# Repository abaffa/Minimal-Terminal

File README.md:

# Baffa Terminal (minimal-terminal clone) 

This is a Simple Terminal board based on "Minimal-Terminal" project by Carsten Herting (oct/2021 https://github.com/slu4coder/Minimal-Terminal).

Current version supports US-International keyboard mapping, four basic serial speeds (115200, 57600, 38400, 9600 BPS) and [supports some basic CSI/Ansi escapes](supported_escapes.md).
 
The prototype board has been tested with my CP/M machine (see http://baffa-2.baffasoft.com.br) but there is another board compatible with RC2014 pinout. 

### Video

## Baffa-2 Terminal Board:

[Order Baffa-2 Minimal Terminal PCB from PCBWay](https://www.pcbway.com/project/shareproject/Baffa_2_Minimal_Terminal_f85704c4.html)

## RC2014 Minimal-Terminal Module

[Order RC2014 Minimal Terminal PCB from PCBWay](https://www.pcbway.com/project/shareproject/RC2014_Minimal_Terminal_41593f8c.html)

## Bill of Materials

| Qty | Value | Parts | Description |
|:---:|:----------:|:-----|:-----|
| 1 |  PINHD-1X20 | JP4 |  PIN HEADER |
| 1 |  PINHD-1X40 | JP3 |  PIN HEADER |
| 6 |  100nf | C2, C6, C9, C10, C11, C12 | CAPACITOR |
| 2 |  10k | R10, R16 | RESISTOR |
| 1 | 150 | R13 | RESISTOR |
| 2 |  1k | R11, R12 | RESISTOR |
| 1 |  24Mhz XTAL |  XTAL |  XTAL SOCKET-14 |
| 1 |  330nf | C1 | CAPACITOR |
| 1 |  47uf | C7 | POLARIZED CAPACITOR |
| 1 |  74HC166N |  IC2 |  8-bit parallel load SHIFT REGISTER |
| 2 | 75 | R14, R15 | RESISTOR, American symbol |
| 1 |  7806T | IC1 |  Positive VOLTAGE REGULATOR |
| 2 |  ATMEGA328P-PU | UART_PS2, VGA |  PDIP-28 Atmel |
| 1 |  BUS UART | JP2 |  JUMPER |
| 1 |  MINI-DIN6PTH |  PS2_DIN |  mini DIN 6 Connector |
| 1 |  Power 9-12v | JP1 |  PIN HEADER |
| 1 |  RESET | S5 | MOM SWITCH |
| 1 |  SPEED | JP7 |  JUMPER |
| 1 | PINHD-1X6 | UART |  PIN HEADER |
| 1 | PINHD-1X6 |  VGA |  PIN HEADER |
| 1 | DSUB | VGA Output | SUB-D |
 
## License

Copyright (c) 2021 Augusto Baffa, Carsten Herting

Permission is hereby granted, free of charge, to any person obtaining a copy
of this software and associated documentation files (the "Software"), to deal
in the Software without restriction, including without limitation the rights
to use, copy, modify, merge, publish, distribute, sublicense, and/or sell
copies of the Software, and to permit persons to whom the Software is
furnished to do so, subject to the following conditions:

The above copyright notice and this permission notice shall be included in all
copies or substantial portions of the Software.

THE SOFTWARE IS PROVIDED "AS IS", WITHOUT WARRANTY OF ANY KIND, EXPRESS OR
IMPLIED, INCLUDING BUT NOT LIMITED TO THE WARRANTIES OF MERCHANTABILITY,
FITNESS FOR A PARTICULAR PURPOSE AND NONINFRINGEMENT. IN NO EVENT SHALL THE
AUTHORS OR COPYRIGHT HOLDERS BE LIABLE FOR ANY CLAIM, DAMAGES OR OTHER
LIABILITY, WHETHER IN AN ACTION OF CONTRACT, TORT OR OTHERWISE, ARISING FROM,
OUT OF OR IN CONNECTION WITH THE SOFTWARE OR THE USE OR OTHER DEALINGS IN THE
SOFTWARE.

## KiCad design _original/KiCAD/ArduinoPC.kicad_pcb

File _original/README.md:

## Original Minimal-Terminal Read.me

Minimal serial UART terminal with VGA and PS2 for up to 230400bps based upon ATmega328P.

This little gadget it ideally suited to be used together with the 'Minimal UART CPU System': https://github.com/slu4coder/Minimal-UART-CPU-System

See the manual section 'Native Tool Chain / Terminal' for more information:
https://docs.google.com/document/d/1c2ZHtLd1BBAwcBAjBZZJmCA3AXpbpv80dlAtsMYpuF4/edit?usp=sharing

---
MIT License

Copyright (c) 2021 Carsten Herting

Permission is hereby granted, free of charge, to any person obtaining a copy
of this software and associated documentation files (the "Software"), to deal
in the Software without restriction, including without limitation the rights
to use, copy, modify, merge, publish, distribute, sublicense, and/or sell
copies of the Software, and to permit persons to whom the Software is
furnished to do so, subject to the following conditions:

The above copyright notice and this permission notice shall be included in all
copies or substantial portions of the Software.

THE SOFTWARE IS PROVIDED "AS IS", WITHOUT WARRANTY OF ANY KIND, EXPRESS OR
IMPLIED, INCLUDING BUT NOT LIMITED TO THE WARRANTIES OF MERCHANTABILITY,
FITNESS FOR A PARTICULAR PURPOSE AND NONINFRINGEMENT. IN NO EVENT SHALL THE
AUTHORS OR COPYRIGHT HOLDERS BE LIABLE FOR ANY CLAIM, DAMAGES OR OTHER
LIABILITY, WHETHER IN AN ACTION OF CONTRACT, TORT OR OTHERWISE, ARISING FROM,
OUT OF OR IN CONNECTION WITH THE SOFTWARE OR THE USE OR OTHER DEALINGS IN THE
SOFTWARE.

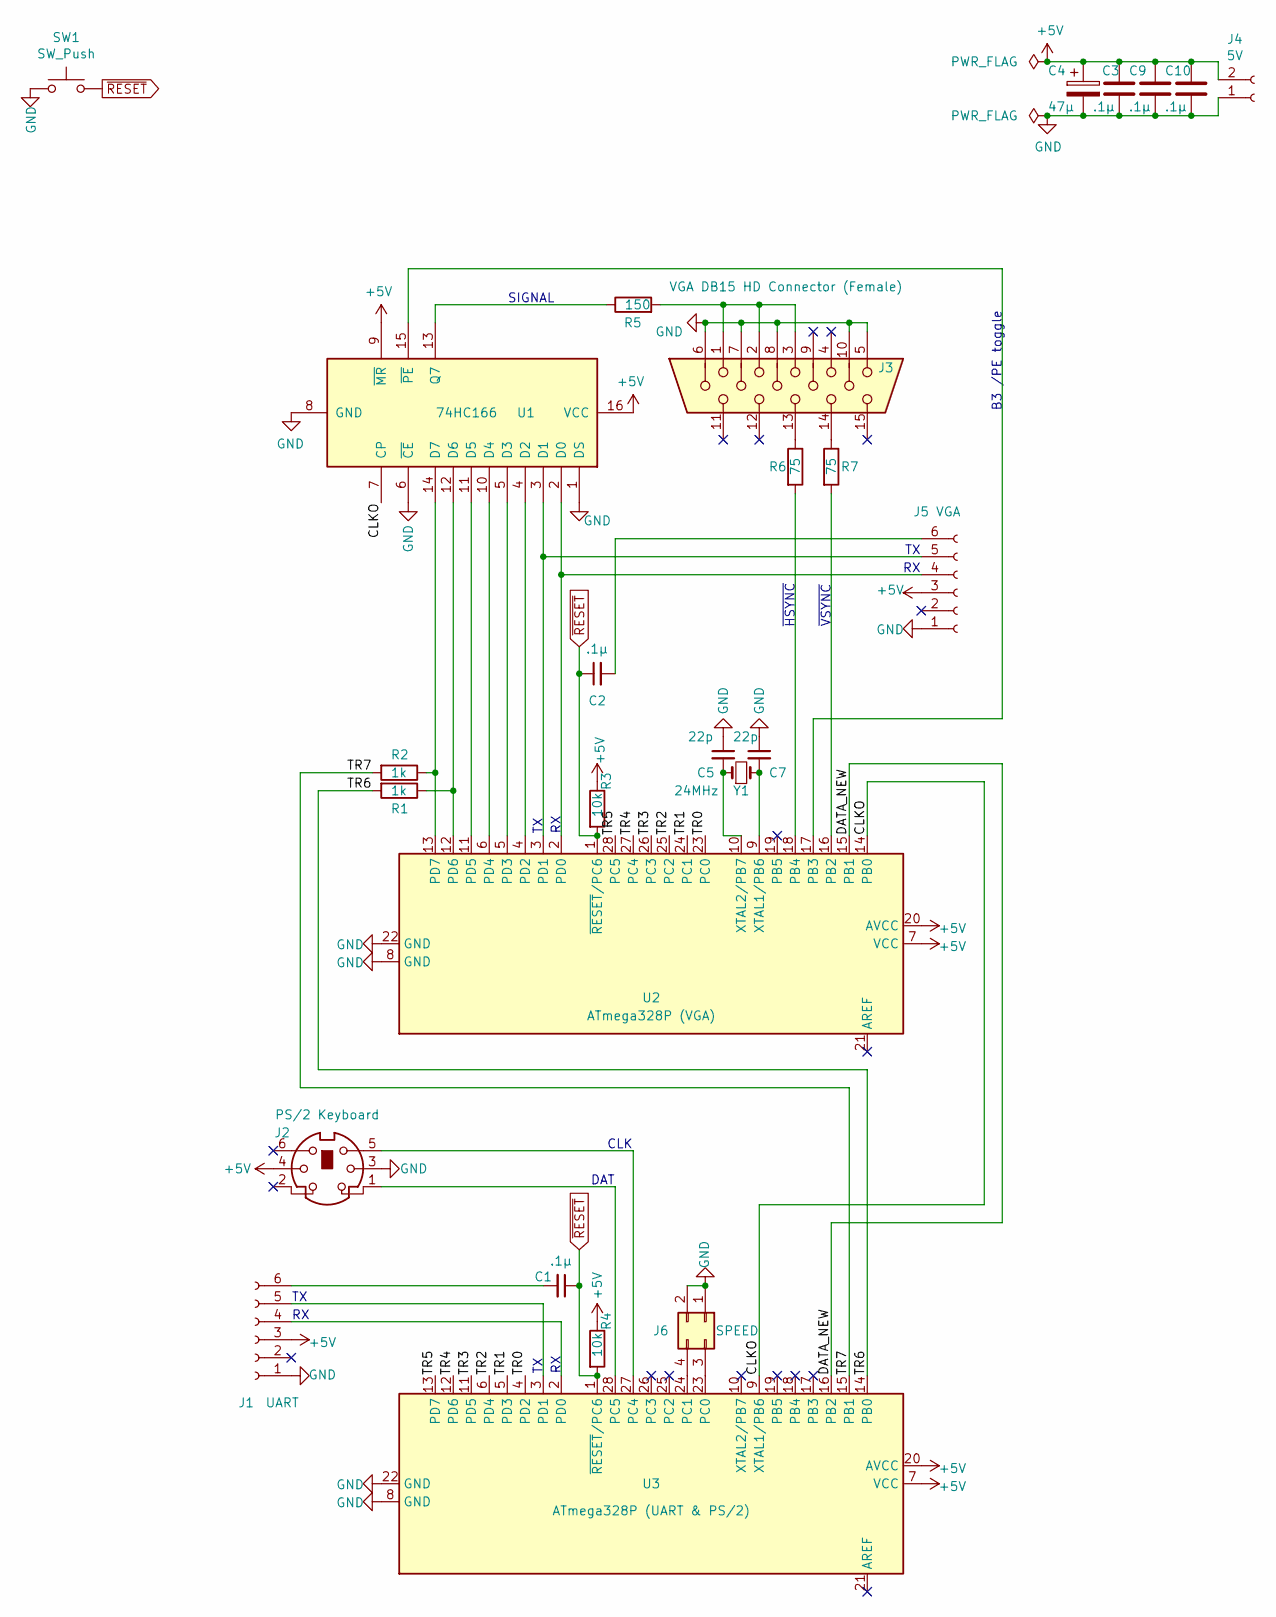
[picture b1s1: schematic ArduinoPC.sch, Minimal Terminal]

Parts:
C1, C2, C4, C9, C10: .1µ; C_Disc_D3.8mm_W2.6mm_P2.50mm
C3: 47µ; CP_Radial_D6.3mm_P2.50mm
C5, C7: 22p; C_Disc_D5.0mm_W2.5mm_P2.50mm
J1: UART; PinSocket_1x06_P2.54mm_Vertical
J2: PS/2 Keyboard; FP_MINI_DIN_6_PS2
J3: VGA DB15 HD Connector (Female); VGA DSUB15HD_female
J4: 5V; PinSocket_1x02_P2.54mm_Vertical
J5: VGA; PinSocket_1x06_P2.54mm_Vertical
J6: SPEED; PinHeader_2x02_P2.54mm_Vertical_Jumper
R1, R2: 1k; R_Axial_DIN0207_L6.3mm_D2.5mm_P7.62mm_Horizontal
R3, R4: 10k; R_Axial_DIN0207_L6.3mm_D2.5mm_P7.62mm_Horizontal
R5: 150; R_Axial_DIN0207_L6.3mm_D2.5mm_P7.62mm_Horizontal
R6, R7: 75; R_Axial_DIN0207_L6.3mm_D2.5mm_P7.62mm_Horizontal
SW1: SW_Push; SW_PUSH_6mm
U1: 74HC166; DIP-16_W7.62mm
U2: ATmega328P (VGA); DIP-28_W7.62mm_Socket
U3: ATmega328P (UART & PS/2); DIP-28_W7.62mm_Socket
Y1: 24MHz; Crystal_HC18-U_Vertical

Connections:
+5V: C3.1, C4.1, C9.1, C10.1, J1.3, J2.4, J4.2, J5.3, R3.1, R4.1, U1.9 (~MR), U1.16 (VCC), U2.7 (VCC), U2.20 (AVCC), U3.7 (VCC), U3.20 (AVCC)
/CLKO: U1.7 (CP), U2.14 (PB0), U3.9 (XTAL1/PB6)
/DATA_NEW: U2.15 (PB1), U3.16 (PB2)
/TR0: U2.23 (PC0), U3.4 (PD2)
/TR1: U2.24 (PC1), U3.5 (PD3)
/TR2: U2.25 (PC2), U3.6 (PD4)
/TR3: U2.26 (PC3), U3.11 (PD5)
/TR4: U2.27 (PC4), U3.12 (PD6)
/TR5: U2.28 (PC5), U3.13 (PD7)
/TR6: R1.2, U3.14 (PB0)
/TR7: R2.2, U3.15 (PB1)
GND: C3.2, C4.2, C5.1, C7.1, C9.2, C10.2, J1.1, J2.3, J3.5, J3.6, J3.7, J3.8, J3.10, J4.1, J5.1, J6.1, J6.2, SW1.1, U1.1 (DS), U1.6 (~CE), U1.8 (GND), U2.8 (GND), U2.22 (GND), U3.8 (GND), U3.22 (GND)
unnamed: C1.2, J1.6
unnamed: C2.2, J5.6
unnamed: C5.2, U2.10 (XTAL2/PB7), Y1.1
unnamed: C7.2, U2.9 (XTAL1/PB6), Y1.2
unnamed: J1.4, U3.2 (PD0)
unnamed: J1.5, U3.3 (PD1)
unnamed: J2.1, U3.28 (PC5)
unnamed: J2.5, U3.27 (PC4)
unnamed: J3.1, J3.2, J3.3, R5.2
unnamed: J3.13, R6.1
unnamed: J3.14, R7.1
unnamed: J5.4, U1.2 (D0), U2.2 (PD0)
unnamed: J5.5, U1.3 (D1), U2.3 (PD1)
unnamed: J6.3, U3.23 (PC0)
unnamed: J6.4, U3.24 (PC1)
unnamed: R1.1, U1.12 (D6), U2.12 (PD6)
unnamed: R2.1, U1.14 (D7), U2.13 (PD7)
unnamed: R5.1, U1.13 (Q7)
unnamed: R6.2, U2.18 (PB4)
unnamed: R7.2, U2.16 (PB2)
unnamed: U1.4 (D2), U2.4 (PD2)
unnamed: U1.5 (D3), U2.5 (PD3)
unnamed: U1.10 (D4), U2.6 (PD4)
unnamed: U1.11 (D5), U2.11 (PD5)
unnamed: U1.15 (~PE), U2.17 (PB3)
~RESET: C1.1, C2.1, R3.2, R4.2, SW1.2, U2.1 (~RESET~/PC6), U3.1 (~RESET~/PC6)

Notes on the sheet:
SIGNAL
~VSYNC
~HSYNC
B3 /PE toggle
DAT
CLK

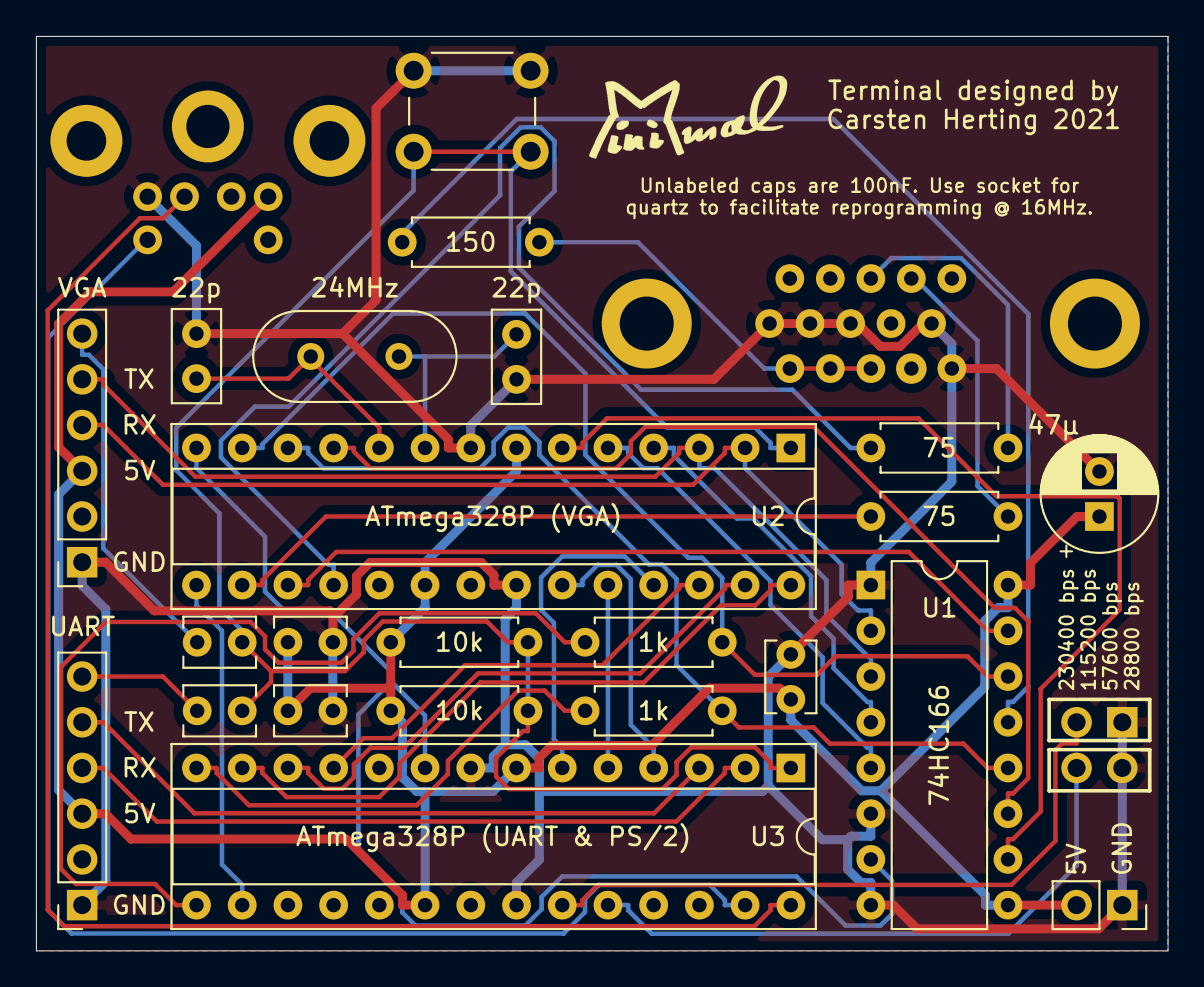
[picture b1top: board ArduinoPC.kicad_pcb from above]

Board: 2 copper layers, 62.9 x 50.8 mm, 26 parts (0 on the bottom side), 38 nets.

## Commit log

2021-12-31 . updating minimal terminal project
2021-12-31 Update README.md
    adding MIT license to Carsten Herting
2021-12-31 Create LICENSE
2022-01-02 . including RC2014 terminal version . margin adjust in README.md pics . adding scan_codes.xlsx
2022-01-06 . Adding Charmap table (char_map.xlsx) . Fixed '^' char bitmap to VGA . Added support to Caps Lock . Fixed Clear Screen CSI Escapes
2022-01-07 . added support to inverse escape ESC[{..}m . fixed inversed ^
2022-01-07 . add new fonts to char_map.xlsx and some chars in fixed default font
2022-01-08 . fixed minor bugs . added support to another escapes and escape parameters separeted by semicolon
2022-01-08 . added splash title on start up . fixed by in \e[1J where cursor at 0,0
2022-01-08 . fixed VGA bitmap for ` (was showing @) . fixed bug on escape \e[r;wH (screen position)
2022-01-08 . added # of lines to \e[#S and \e[#T
2022-01-08 . adding num lock support
2022-01-08 . updating eagle files with last fixes.
2022-01-09 . fixed ctrl \ (ibm layout keyboard with extra \ key between shift and z keys) . fixed ESC[J2 - must clear screen and set cursor position to 0,0
2022-02-20 . bit time fix in send command byte - it was causing problems with some keyboards
2022-05-28 . gerbers updated . added new images
2022-05-28 . adding schematics
2022-05-28 . updating README.md
2022-07-28 . adding apple 1 and apple ][ charmap
2022-07-29 adding prototype ugly pics :D

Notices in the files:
_original/KiCAD/ArduinoPC.sch:
creativecommons.org/licenses/by-nc-sa/3.0/deed.en
License: CC BY-NC-SA 3.0
